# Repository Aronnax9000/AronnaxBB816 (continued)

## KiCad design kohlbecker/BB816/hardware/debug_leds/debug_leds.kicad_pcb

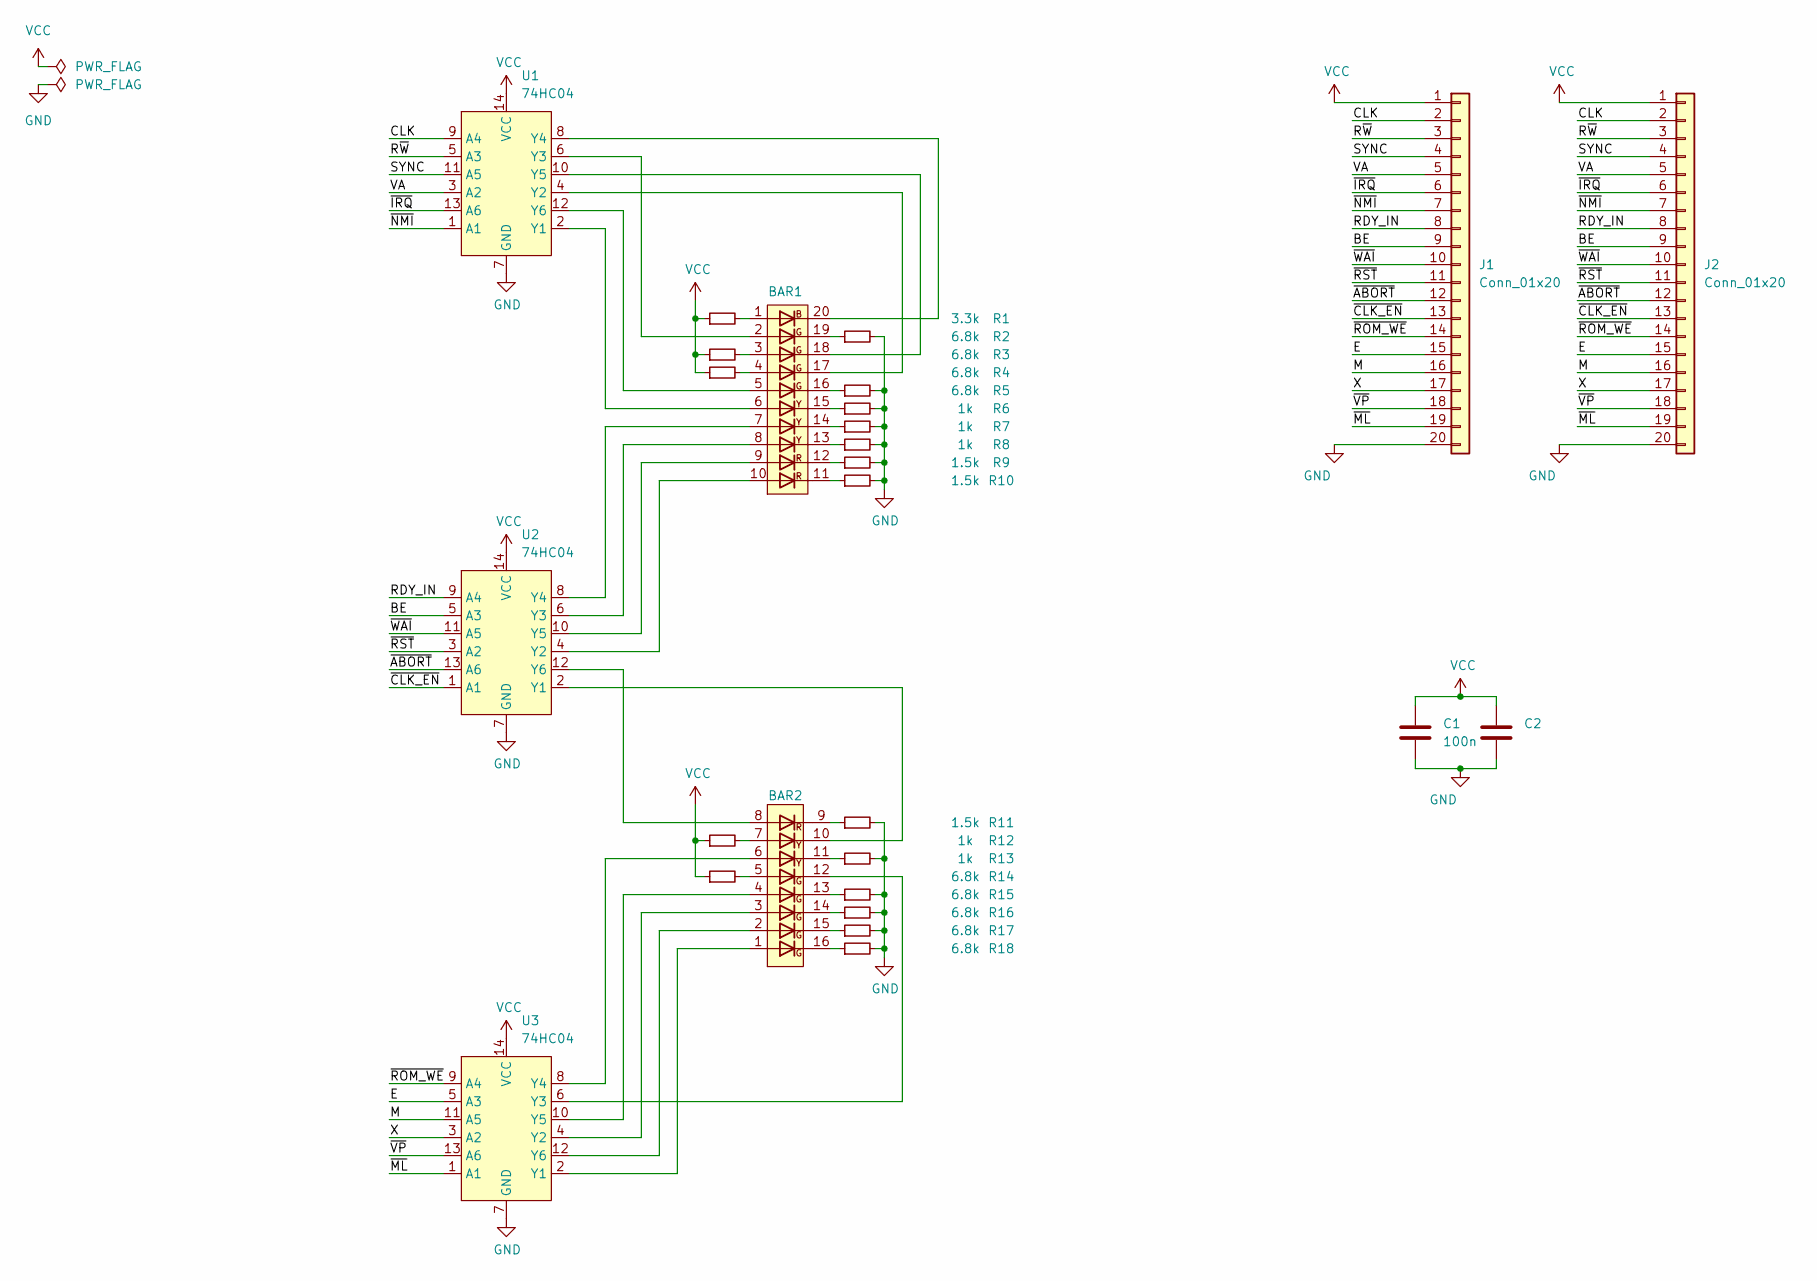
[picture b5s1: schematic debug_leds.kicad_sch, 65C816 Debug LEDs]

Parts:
BAR1: LED-Array-10-BGYR; DIP-20_W7.62mm
BAR2: LED-Array-8-GYR; DIP-16_W7.62mm
C1, C2: 100n; C_Disc_D3.0mm_W1.6mm_P2.50mm
J1, J2: Conn_01x20; PinHeader_1x20_P2.54mm_Vertical
R1: 3.3k; R_1206_3216Metric_Pad1.30x1.75mm_HandSolder
R2, R3, R4, R5, R14, R15, R16, R17, R18: 6.8k; R_1206_3216Metric_Pad1.30x1.75mm_HandSolder
R6, R7, R8, R12, R13: 1k; R_1206_3216Metric_Pad1.30x1.75mm_HandSolder
R9, R10, R11: 1.5k; R_1206_3216Metric_Pad1.30x1.75mm_HandSolder
U1, U2, U3: 74HC04; DIP-14_W7.62mm

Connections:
/BE: J1.9, J2.9, U2.5 (A3)
/CLK: J1.2, J2.2, U1.9 (A4)
/E: J1.15, J2.15, U3.5 (A3)
/M: J1.16, J2.16, U3.11 (A5)
/RDY_IN: J1.8, J2.8, U2.9 (A4)
/R~W: J1.3, J2.3, U1.5 (A3)
/SYNC: J1.4, J2.4, U1.11 (A5)
/VA: J1.5, J2.5, U1.3 (A2)
/X: J1.17, J2.17, U3.3 (A2)
/~ABORT: J1.12, J2.12, U2.13 (A6)
/~CLK_EN: J1.13, J2.13, U2.1 (A1)
/~IRQ: J1.6, J2.6, U1.13 (A6)
/~ML: J1.19, J2.19, U3.1 (A1)
/~NMI: J1.7, J2.7, U1.1 (A1)
/~ROM_WE: J1.14, J2.14, U3.9 (A4)
/~RST: J1.11, J2.11, U2.3 (A2)
/~VP: J1.18, J2.18, U3.13 (A6)
/~WAI: J1.10, J2.10, U2.11 (A5)
GND: C1.2, C2.2, J1.20, J2.20, R2.2, R5.2, R6.2, R7.2, R8.2, R9.2, R10.2, R11.2, R13.2, R15.2, R16.2, R17.2, R18.2, U1.7 (GND), U2.7 (GND), U3.7 (GND)
unnamed: BAR1.1 (A), R1.2
unnamed: BAR1.3 (A), R3.2
unnamed: BAR1.4 (A), R4.2
unnamed: BAR1.11 (K), R10.1
unnamed: BAR1.12 (K), R9.1
unnamed: BAR1.13 (K), R8.1
unnamed: BAR1.14 (K), R7.1
unnamed: BAR1.15 (K), R6.1
unnamed: BAR1.16 (K), R5.1
unnamed: BAR1.19 (K), R2.1
unnamed: BAR2.5 (A), R14.2
unnamed: BAR2.7 (A), R12.2
unnamed: BAR2.9 (K), R11.1
unnamed: BAR2.11 (K), R13.1
unnamed: BAR2.13 (K), R15.1
unnamed: BAR2.14 (K), R16.1
unnamed: BAR2.15 (K), R17.1
unnamed: BAR2.16 (K), R18.1
unnamed: BAR1.6 (A), U1.2 (Y1)
unnamed: BAR1.17 (K), U1.4 (Y2)
unnamed: BAR1.2 (A), U1.6 (Y3)
unnamed: BAR1.20 (K), U1.8 (Y4)
unnamed: BAR1.18 (K), U1.10 (Y5)
unnamed: BAR1.5 (A), U1.12 (Y6)
unnamed: BAR2.10 (K), U2.2 (Y1)
unnamed: BAR1.10 (A), U2.4 (Y2)
unnamed: BAR1.8 (A), U2.6 (Y3)
unnamed: BAR1.7 (A), U2.8 (Y4)
unnamed: BAR1.9 (A), U2.10 (Y5)
unnamed: BAR2.8 (A), U2.12 (Y6)
unnamed: BAR2.1 (A), U3.2 (Y1)
unnamed: BAR2.3 (A), U3.4 (Y2)
unnamed: BAR2.12 (K), U3.6 (Y3)
unnamed: BAR2.6 (A), U3.8 (Y4)
unnamed: BAR2.4 (A), U3.10 (Y5)
unnamed: BAR2.2 (A), U3.12 (Y6)
VCC: C1.1, C2.1, J1.1, J2.1, R1.1, R3.1, R4.1, R12.1, R14.1, U1.14 (VCC), U2.14 (VCC), U3.14 (VCC)

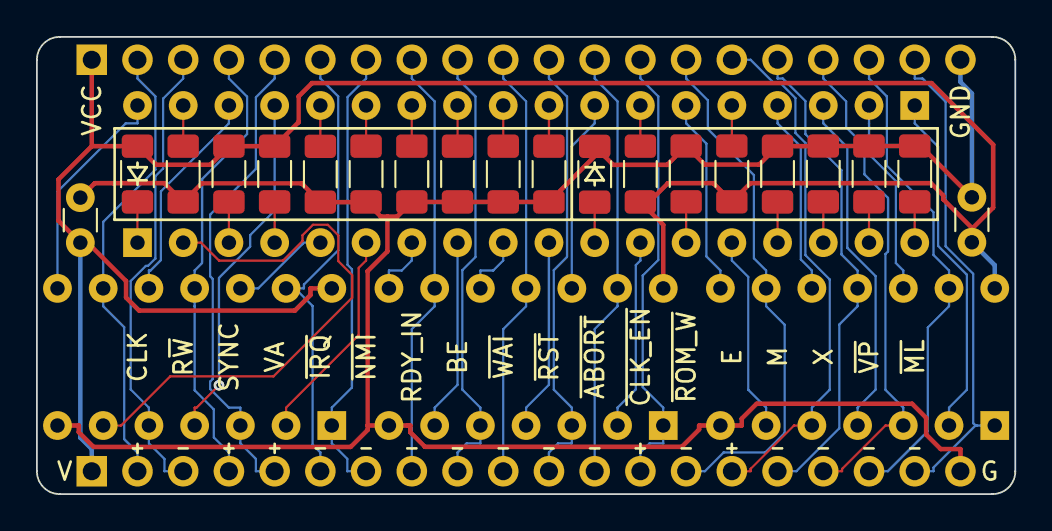
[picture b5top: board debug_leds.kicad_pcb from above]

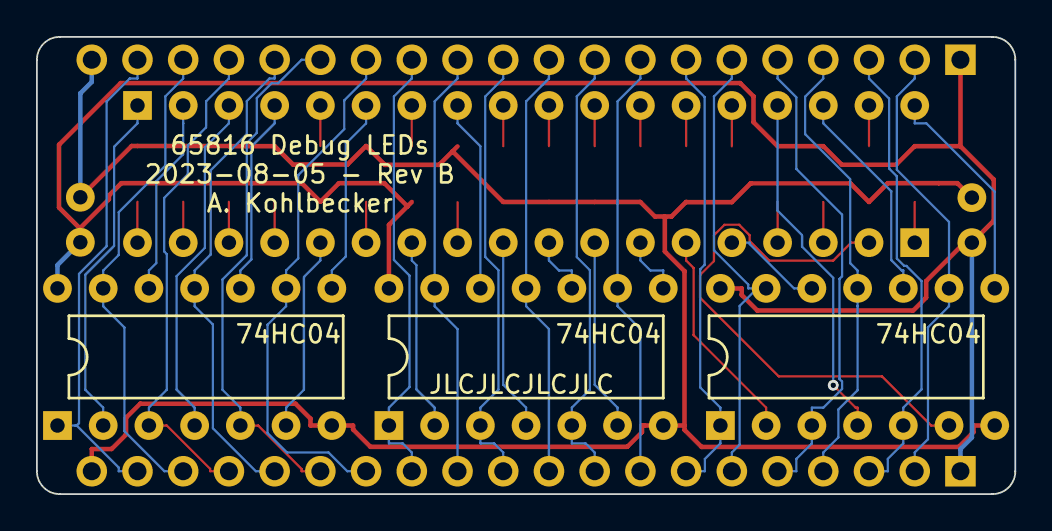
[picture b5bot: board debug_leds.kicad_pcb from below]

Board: 2 copper layers, 54.4 x 25.4 mm, 27 parts (5 on the bottom side), 56 nets.

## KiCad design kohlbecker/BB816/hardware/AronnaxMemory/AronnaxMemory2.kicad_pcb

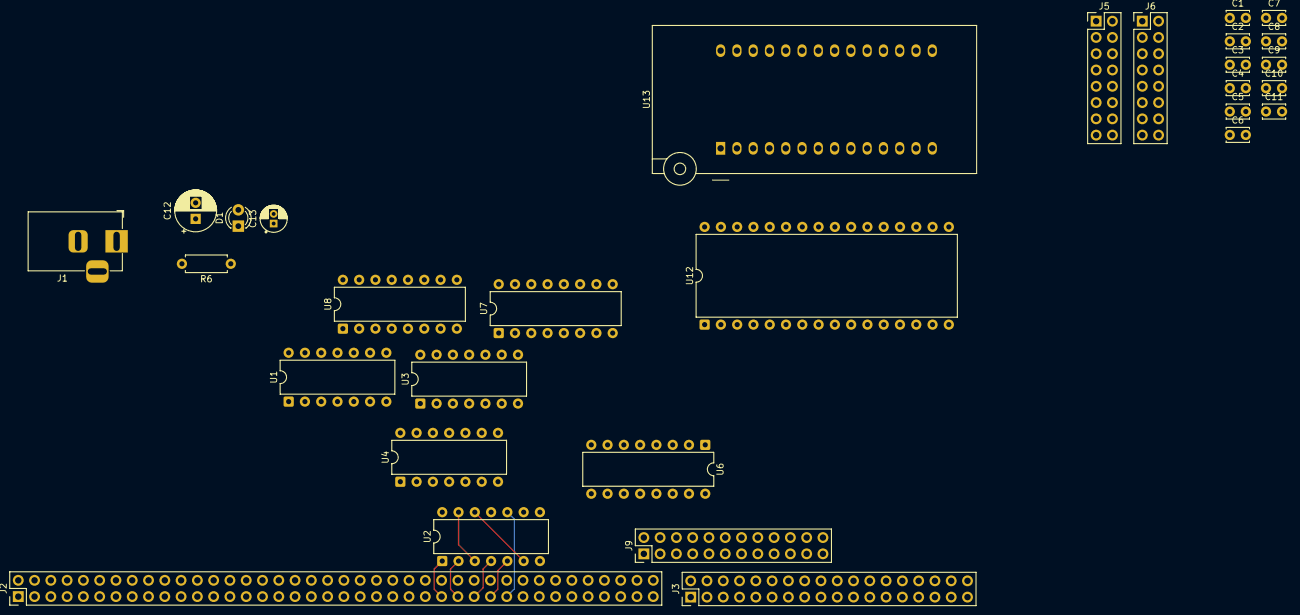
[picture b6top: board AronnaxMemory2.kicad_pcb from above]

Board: 2 copper layers, 30 parts (0 on the bottom side), 69 nets.

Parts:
C1, C2, C3, C4, C5, C6, C7, C8, C9, C10, C11: 100nF; C_Disc_D3.4mm_W2.1mm_P2.50mm
C12: 220u; CP_Radial_D6.3mm_P2.50mm
C13: 10u; CP_Radial_D4.0mm_P1.50mm
D1: POWER; LED_D3.0mm
J1: Barrel_Jack_Switch; BarrelJack_Horizontal
J2: Conn_02x40_Odd_Even; PinHeader_2x40_P2.54mm_Vertical
J3: Conn_02x18_Odd_Even; PinHeader_2x18_P2.54mm_Vertical
J5: I/O ~{CS}; PinHeader_2x08_P2.54mm_Vertical
J6: ADDR; PinHeader_2x08_P2.54mm_Vertical
J9: Vector Rewrite; PinHeader_2x12_P2.54mm_Vertical
R6: 1k; R_Axial_DIN0207_L6.3mm_D2.5mm_P7.62mm_Horizontal
U1: 74LS04; DIP-14_W7.62mm
U2, U3: 74LS32; DIP-14_W7.62mm
U4: 74LS08; DIP-14_W7.62mm
U6, U7, U8: 74LS138; DIP-16_W7.62mm
U12: AS6C4008-55PCN; DIP-32_W15.24mm
U13: AT28C256-15PC; DIP_Socket-28_W11.9_W12.7_W15.24_W17.78_W18.5_3M_228-1277-0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

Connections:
/A0: J3.19, U12.12 (A0), U13.10 (A0)
/A1: J9.15, U12.11 (A1), U13.9 (A1)
/A2: J9.13, U12.10 (A2), U13.8 (A2)
/A3: J9.11, U12.9 (A3), U13.7 (A3)
/A4: J9.9, U12.8 (A4), U13.6 (A4)
/A5: J3.9, U8.1 (A0), U12.7 (A5), U13.5 (A5)
/A6: J3.7, U8.2 (A1), U12.6 (A6), U13.4 (A6)
/A7: J3.5, U8.3 (A2), U12.5 (A7), U13.3 (A7)
/A8: J3.3, U7.1 (A0), U12.27 (A8), U13.25 (A8)
/A9: J3.1, U7.2 (A1), U12.26 (A9), U13.24 (A9)
/A10: J2.79, U7.3 (A2), U12.23 (A10), U13.21 (A10)
/A11: J2.77, U6.1 (A0), U7.5 (E2), U12.25 (A11), U13.23 (A11)
/A12: J2.75, U6.2 (A1), U12.4 (A12), U13.2 (A12)
/A13: J2.73, U6.3 (A2), U12.28 (A13), U13.26 (A13)
/A14: J2.71, U6.5 (E2), U12.3 (A14), U13.1 (A14)
/A15: J2.69, U1.5, U3.10, U12.31 (A15)
/A16: J2.67, U12.2 (A16)
/A17: J2.65, U12.30 (A17)
/A18: J2.63, U12.1 (A18)
/A19: J2.61, U2.10
/A20: J2.59, U2.5
/A21: J2.57, U2.4
/A22: J2.55, U2.2
/A23: J2.53, U2.1
/AA1: J3.17, J9.24
/AA2: J3.15, J9.22
/AA3: J3.13, J9.20
/AA4: J3.11, J9.18
/D0: J3.35, U12.13 (DQ0), U13.11 (D0)
/D1: J3.33, U12.14 (DQ1), U13.12 (D1)
/D2: J3.31, U12.15 (DQ2), U13.13 (D2)
/D3: J3.29, U12.17 (DQ3), U13.15 (D3)
/D4: J3.27, U12.18 (DQ4), U13.16 (D4)
/D5: J3.25, U12.19 (DQ5), U13.17 (D5)
/D6: J3.23, U12.20 (DQ6), U13.18 (D6)
/D7: J3.21, U12.21 (DQ7), U13.19 (D7)
/E: J2.43, J9.6, U1.3, U4.2
/~BANK0: J2.41, U3.5, U3.9
/~VP: J2.49, J9.8
/~WR: J2.39, U12.29 (WE#), U13.27 (~WE)
GND: C1.2, C2.2, C3.2, C4.2, C5.2, C6.2, C7.2, C8.2, C9.2, C10.2, C11.2, C12.2, C13.2, D1.1 (K), J1.2, J2.2, J2.3, J2.4, J2.6, J2.8, J2.10, J2.12, J2.14, J2.16, J2.18, J2.20, J2.22, J2.24, J2.26, J2.28, J2.30, J2.32, J2.34, J2.36, J2.38, J2.40, J2.42, J2.44, J2.46, J2.48, J2.50, J2.52, J2.54, J2.56, J2.58, J2.60, J2.62, J2.64, J2.66, J2.68, J2.70, J2.72, J2.74, J2.76, J2.78, J2.80, J3.2, J3.4, J3.6, J3.8, J3.10, J3.12, J3.14, J3.16, J3.18, J3.20, J3.22, J3.24, J3.26, J3.28, J3.30, J3.32, J3.34, J3.36, J5.2, J5.4, J5.6, J5.8, J5.10, J5.12, J5.14, J5.16, J6.2, J6.4, J6.6, J6.8, J6.10, J6.12, J6.14, J6.16, J9.1, J9.2, J9.3, J9.5, J9.7, J9.10, J9.12, J9.14, J9.16, U1.7 (GND), U1.13, U2.7 (GND), U3.7 (GND), U4.4, U4.5, U4.7 (GND), U4.9, U4.10, U4.12, U4.13, U12.16 (VSS), U13.14 (GND)
MEG0_LO: J6.3, U1.2
unnamed: D1.2 (A), R6.1
unnamed: J9.17, J9.19, J9.21, J9.23
unnamed: U1.4, U3.1
unnamed: U1.6, U3.4
unnamed: U1.8, U4.1
unnamed: U1.10, U3.13
unnamed: U2.9, U2.11
unnamed: U2.6, U2.12
unnamed: U2.3, U2.13
unnamed: U3.12, U4.3
unnamed: U6.15 (O0), U7.4 (E1)
unnamed: U8.4 (E1), U8.8 (GND)
unnamed: U3.11, U12.24 (OE#)
VCC: C1.1, C2.1, C3.1, C4.1, C5.1, C6.1, C7.1, C8.1, C9.1, C10.1, C11.1, C12.1, C13.1, J1.1, J2.1, J9.4, R6.2, U1.14 (VCC), U2.14 (VCC), U3.14 (VCC), U4.14 (VCC), U6.6 (E3), U6.16 (VCC), U7.6 (E3), U7.16 (VCC), U8.6 (E3), U8.16 (VCC), U12.32 (VCC), U13.28 (VCC)
~0x00: J5.15, U8.15 (O0)
~0x20: J5.13, U8.14 (O1)
~0x40: J5.11, U8.13 (O2)
~0x60: J5.9, U8.12 (O3)
~0x80: J5.7, U8.11 (O4)
~0xA0: J5.5, U8.10 (O5)
~0xCO: J5.3, U8.9 (O6)
~0xE0: J5.1, U8.7 (O7)
~BANK0_HI: J6.9, U1.9, U3.2, U3.6, U13.20 (~CS)
~BANK0_LO: J6.11, U3.8, U6.4 (E1)
~MEG0_LO: J6.1, U1.1, U2.8, U12.22 (CE#)
~PAGE1: J6.15, U1.11, U7.14 (O1), U8.5 (E2)
~ROM_OE: J6.13, U3.3, U13.22 (~OE)

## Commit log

2025-03-11 Add original Kohlbecker snapshot.
2025-03-11 Resaved all Kohlbecker files in Kicad 9
2025-03-11 First big Aronnax push.
2025-03-11 memPush
2025-03-11 Before deleting high memory
2025-03-11 Before eliminating hi 512kb
2025-03-11 Ready update schematic with added components to breakout
2025-03-11 Before PCB update
2025-03-11 More preening.
2025-03-13 New pcb
2025-03-13 All of it.
2025-03-17 Memory
2025-03-17 getting ready to add VPB rewrite
2025-03-17 Saves
2025-03-18 Cleanup
2025-04-03 ATF22V10
2025-04-03 PLAs for Days! Also Vector Rewrite
2025-04-04 Heal board
2025-04-05 Everything, except the plot.
2025-04-07 Pare
2025-04-07 Refactor project.
2025-04-15 All of it
2025-04-15 All of it p2
2025-04-15 All of it v3
2025-04-16 Before replacing 22V10 with 4 bit adder
2025-04-17 Gettin ready to publish
2025-04-17 Simplifying Removed VPR
2025-04-20 Before removing RAM
2025-05-06 May 2025
2025-05-12 Sync to Ace
